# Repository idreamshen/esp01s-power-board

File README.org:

* ESP01S Power Board
ESP01s 供电底板

* EDA 软件
KiCAD 8.0.7
(docker image: linuxserver/kicad:8.0.7)

* PCB 图
[[/images/pcb1.png]]
[[/images/pcb2.png]]

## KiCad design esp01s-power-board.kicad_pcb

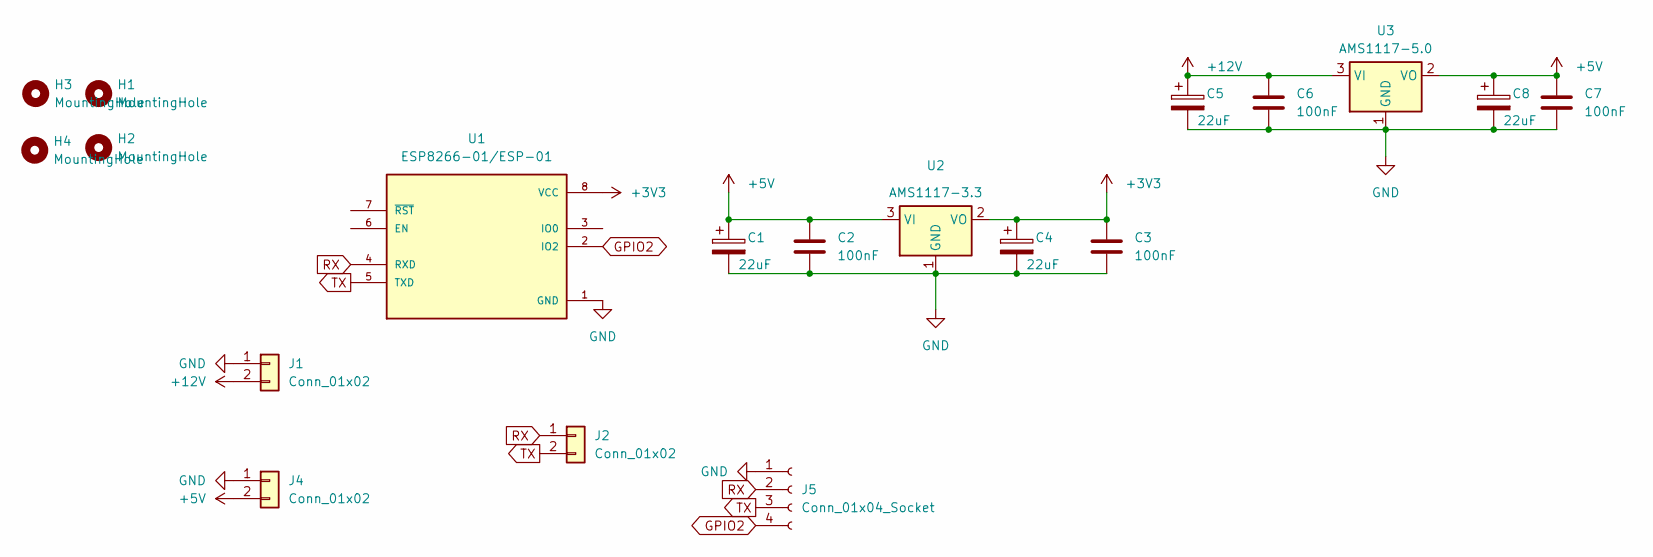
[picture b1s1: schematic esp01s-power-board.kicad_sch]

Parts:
C1, C4, C5, C8: 22uF; CP_EIA-3528-21_Kemet-B
C2, C3, C6, C7: 100nF; C_0603_1608Metric
H1, H2, H3, H4: MountingHole; MountingHole_3.2mm_M3
J1, J2, J4: Conn_01x02; JST_XH_B2B-XH-A_1x02_P2.50mm_Vertical
J5: Conn_01x04_Socket; PinSocket_1x04_P2.54mm_Vertical
U1: ESP8266-01/ESP-01; XCVR_ESP8266-01_ESP-01; PARTREV V1.2
U2: AMS1117-3.3; SOT-223-3_TabPin2
U3: AMS1117-5.0; SOT-223-3_TabPin2

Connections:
+3V3: C3.1, C4.1, U1.8 (VCC), U2.2 (VO)
+5V: C1.1, C2.1, C7.1, C8.1, J4.2, U2.3 (VI), U3.2 (VO)
+12V: C5.1, C6.1, J1.2, U3.3 (VI)
GND: C1.2, C2.2, C3.2, C4.2, C5.2, C6.2, C7.2, C8.2, J1.1, J4.1, J5.1, U1.1 (GND), U2.1 (GND), U3.1 (GND)
GPIO2: J5.4, U1.2 (IO2)
RX: J2.1, J5.2, U1.4 (RXD)
TX: J2.2, J5.3, U1.5 (TXD)

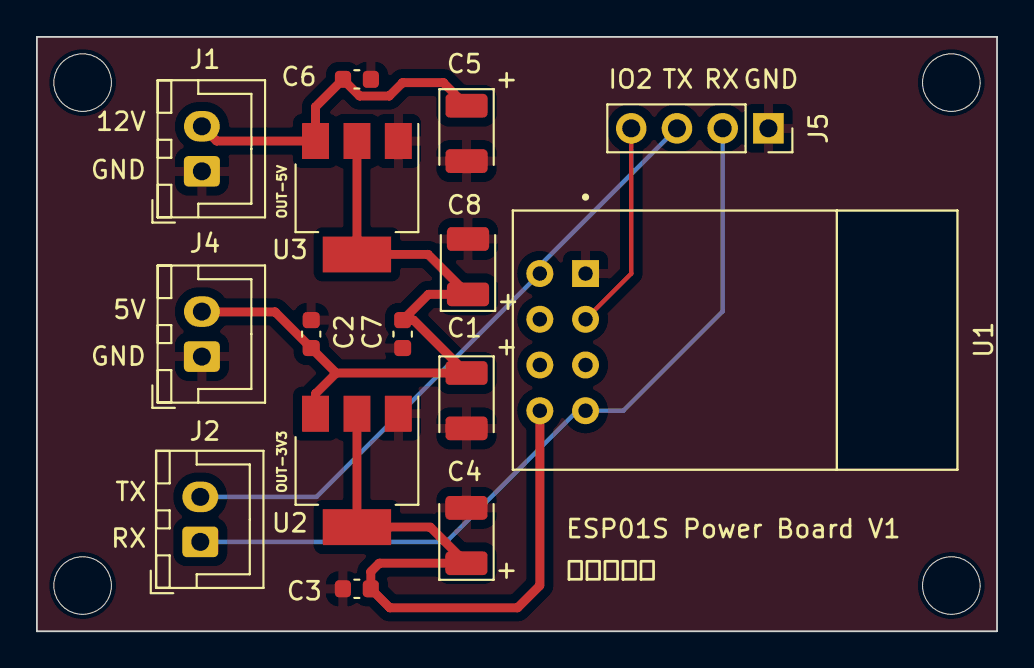
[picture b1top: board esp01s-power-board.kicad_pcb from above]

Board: 2 copper layers, 53.3 x 33.0 mm, 19 parts (0 on the bottom side), 7 nets.

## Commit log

2024-12-13 init
2024-12-13 add README
2024-12-13 save
2024-12-18 add images
2024-12-18 add software
